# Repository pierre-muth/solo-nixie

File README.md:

# solo-nixie
A tiny single nixie tube clock, for LD995a or IN-16. USB powered, DS3231 RTC, built-in power-supply.

Details here https://pierremuth.wordpress.com/2021/12/11/a-cute-little-single-tube-nixie-clock/

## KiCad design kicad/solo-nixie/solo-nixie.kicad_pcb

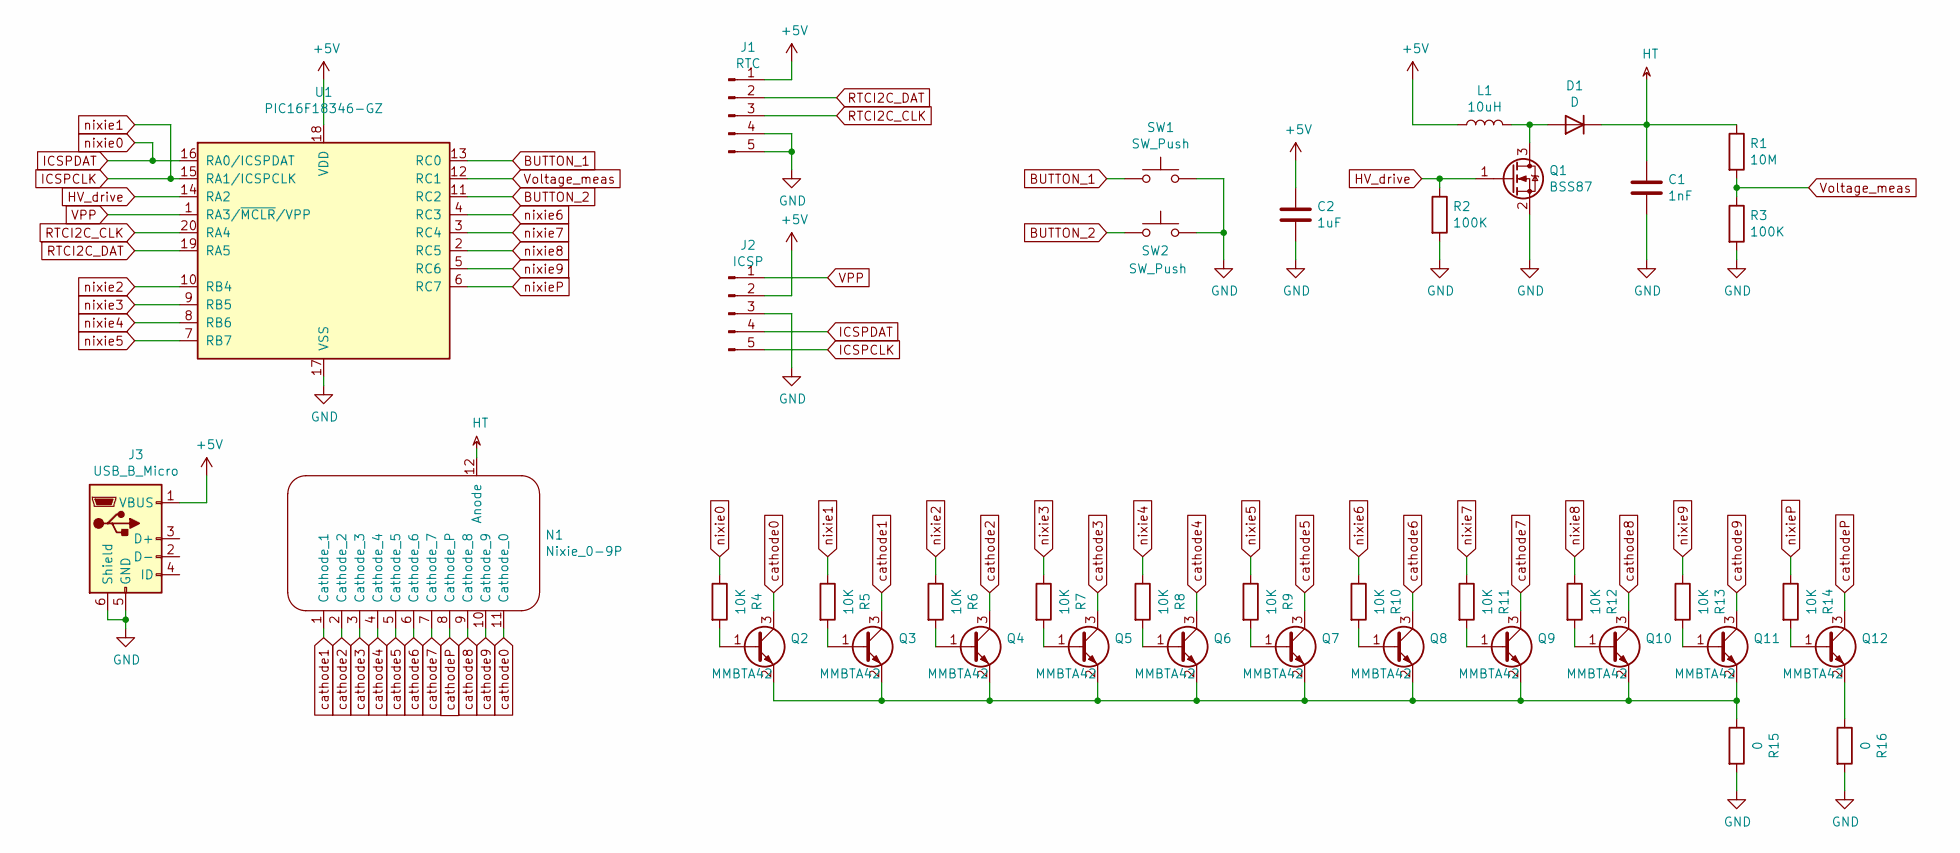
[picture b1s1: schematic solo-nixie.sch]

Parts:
C1: 1nF; 0805_HandSoldering
C2: 1uF; 0805_HandSoldering
D1: D; D_3220
J1: RTC; Pin_Header_RTC_5x2.54mm_SMD
J2: ICSP; PinHeader_1x05_P1.27mm_Vertical
J3: USB_B_Micro; USB_Micro-B_Wuerth-629105150521_CircularHoles
L1: 10uH; L_3216Metric
N1: Nixie_0-9P; LD8007
Q1: BSS87; CPH3
Q2, Q3, Q4, Q5, Q6, Q7, Q8, Q9, Q10, Q11, Q12: MMBTA42; SOT-23
R1: 10M; 0805_HandSoldering
R2, R3: 100K; 0805_HandSoldering
R4, R5, R6, R7, R8, R9, R10, R11, R12, R13, R14: 10K; 0805_HandSoldering
R15, R16: 0; 0805_HandSoldering
SW1, SW2: SW_Push; SW_SPST_EVQP7A
U1: PIC16F18346-GZ; UQFN-20-1EP_4x4mm_P0.5mm_EP2.8x2.8mm

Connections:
+5V: C2.1, J1.1, J2.2, J3.1 (VBUS), L1.1, U1.18 (VDD); also elsewhere on the board
BUTTON_1: SW1.1, U1.13 (RC0)
BUTTON_2: SW2.1, U1.11 (RC2)
GND: C1.2, C2.2, J1.4, J1.5, J2.3, J3.5 (GND), J3.6 (Shield), Q1.2 (S), R2.2, R3.2, R15.2, R16.2, SW1.2, SW2.2, U1.17 (VSS); also elsewhere on the board
HT: C1.1, D1.1 (K), N1.12 (Anode), R1.1
HV_drive: Q1.1 (G), R2.1, U1.14 (RA2)
ICSPCLK: J2.5, R5.1, U1.15 (RA1/ICSPCLK)
ICSPDAT: J2.4, R4.1, U1.16 (RA0/ICSPDAT)
unnamed: D1.2 (A), L1.2, Q1.3 (D)
unnamed: Q2.1 (B), R4.2
unnamed: Q3.1 (B), R5.2
unnamed: Q4.1 (B), R6.2
unnamed: Q5.1 (B), R7.2
unnamed: Q6.1 (B), R8.2
unnamed: Q7.1 (B), R9.2
unnamed: Q8.1 (B), R10.2
unnamed: Q9.1 (B), R11.2
unnamed: Q10.1 (B), R12.2
unnamed: Q2.2 (E), Q3.2 (E), Q4.2 (E), Q5.2 (E), Q6.2 (E), Q7.2 (E), Q8.2 (E), Q9.2 (E), Q10.2 (E), Q11.2 (E), R15.1
unnamed: Q11.1 (B), R13.2
unnamed: Q12.1 (B), R14.2
unnamed: Q12.2 (E), R16.1
RTCI2C_CLK: J1.3, U1.20 (RA4); also elsewhere on the board
RTCI2C_DAT: J1.2, U1.19 (RA5); also elsewhere on the board
VPP: J2.1, U1.1 (RA3/~MCLR~/VPP)
Voltage_meas: R1.2, R3.1, U1.12 (RC1)
cathode0: N1.11 (Cathode_0), Q2.3 (C)
cathode1: N1.1 (Cathode_1), Q3.3 (C)
cathode2: N1.2 (Cathode_2), Q4.3 (C)
cathode3: N1.3 (Cathode_3), Q5.3 (C)
cathode4: N1.4 (Cathode_4), Q6.3 (C)
cathode5: N1.5 (Cathode_5), Q7.3 (C)
cathode6: N1.6 (Cathode_6), Q8.3 (C)
cathode7: N1.7 (Cathode_7), Q9.3 (C)
cathode8: N1.9 (Cathode_8), Q10.3 (C)
cathode9: N1.10 (Cathode_9), Q11.3 (C)
cathodeP: N1.8 (Cathode_P), Q12.3 (C)
nixie2: R6.1, U1.10 (RB4)
nixie3: R7.1, U1.9 (RB5)
nixie4: R8.1, U1.8 (RB6)
nixie5: R9.1, U1.7 (RB7)
nixie6: R10.1, U1.4 (RC3)
nixie7: R11.1, U1.3 (RC4)
nixie8: R12.1, U1.2 (RC5)
nixie9: R13.1, U1.5 (RC6)
nixieP: R14.1, U1.6 (RC7)

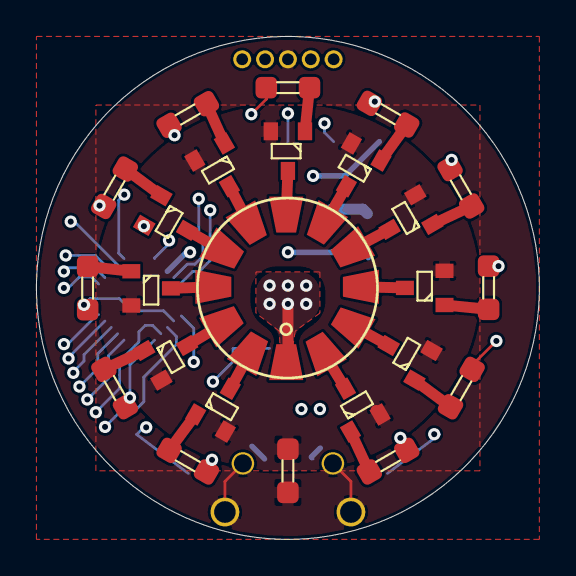
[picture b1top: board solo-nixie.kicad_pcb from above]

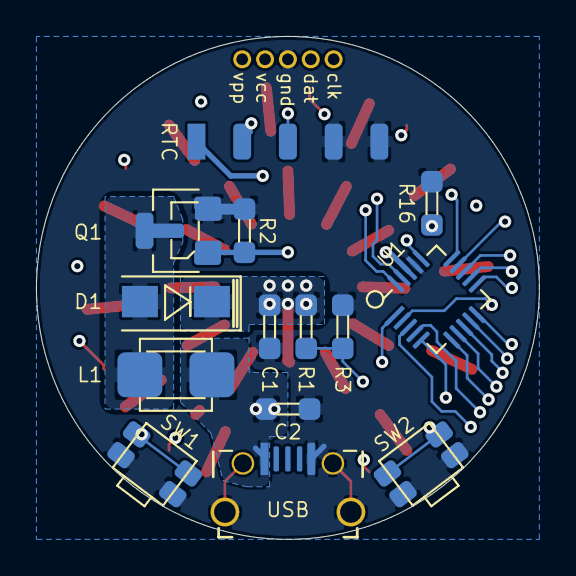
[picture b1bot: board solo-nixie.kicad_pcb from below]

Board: 4 copper layers, 27.9 x 27.9 mm, 39 parts (15 on the bottom side), 46 nets.

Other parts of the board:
RTC: RTC; Pin_Header_RTC_5x2.54mm_SMD
USB: USB_B_Micro; USB_Micro-B_Wuerth-629105150521_CircularHoles

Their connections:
+5V: RTC.1, USB.1; also elsewhere on the board
GND: RTC.4, RTC.5, USB.5, USB.6; also elsewhere on the board
RTCI2C_CLK: RTC.3; also elsewhere on the board
RTCI2C_DAT: RTC.2; also elsewhere on the board

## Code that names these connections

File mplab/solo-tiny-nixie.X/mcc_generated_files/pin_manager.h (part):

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// get/set nixie0 aliases
#define nixie0_TRIS                 TRISAbits.TRISA0
#define nixie0_LAT                  LATAbits.LATA0
#define nixie0_PORT                 PORTAbits.RA0
#define nixie0_WPU                  WPUAbits.WPUA0
#define nixie0_OD                   ODCONAbits.ODCA0
#define nixie0_ANS                  ANSELAbits.ANSA0
#define nixie0_SetHigh()            do { LATAbits.LATA0 = 1; } while(0)
#define nixie0_SetLow()             do { LATAbits.LATA0 = 0; } while(0)
#define nixie0_Toggle()             do { LATAbits.LATA0 = ~LATAbits.LATA0; } while(0)
#define nixie0_GetValue()           PORTAbits.RA0
#define nixie0_SetDigitalInput()    do { TRISAbits.TRISA0 = 1; } while(0)
#define nixie0_SetDigitalOutput()   do { TRISAbits.TRISA0 = 0; } while(0)
#define nixie0_SetPullup()          do { WPUAbits.WPUA0 = 1; } while(0)
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// get/set nixie1 aliases
#define nixie1_TRIS                 TRISAbits.TRISA1
#define nixie1_LAT                  LATAbits.LATA1
#define nixie1_PORT                 PORTAbits.RA1
#define nixie1_WPU                  WPUAbits.WPUA1
#define nixie1_OD                   ODCONAbits.ODCA1
#define nixie1_ANS                  ANSELAbits.ANSA1
#define nixie1_SetHigh()            do { LATAbits.LATA1 = 1; } while(0)
#define nixie1_SetLow()             do { LATAbits.LATA1 = 0; } while(0)
#define nixie1_Toggle()             do { LATAbits.LATA1 = ~LATAbits.LATA1; } while(0)
#define nixie1_GetValue()           PORTAbits.RA1
#define nixie1_SetDigitalInput()    do { TRISAbits.TRISA1 = 1; } while(0)
#define nixie1_SetDigitalOutput()   do { TRISAbits.TRISA1 = 0; } while(0)
#define nixie1_SetPullup()          do { WPUAbits.WPUA1 = 1; } while(0)
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#define RA2_SetHigh()            do { LATAbits.LATA2 = 1; } while(0)
#define RA2_SetLow()             do { LATAbits.LATA2 = 0; } while(0)
#define RA2_Toggle()             do { LATAbits.LATA2 = ~LATAbits.LATA2; } while(0)
#define RA2_GetValue()              PORTAbits.RA2
#define RA2_SetDigitalInput()    do { TRISAbits.TRISA2 = 1; } while(0)
#define RA2_SetDigitalOutput()   do { TRISAbits.TRISA2 = 0; } while(0)
#define RA2_SetPullup()             do { WPUAbits.WPUA2 = 1; } while(0)
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#define RA4_SetHigh()            do { LATAbits.LATA4 = 1; } while(0)
#define RA4_SetLow()             do { LATAbits.LATA4 = 0; } while(0)
#define RA4_Toggle()             do { LATAbits.LATA4 = ~LATAbits.LATA4; } while(0)
#define RA4_GetValue()              PORTAbits.RA4
#define RA4_SetDigitalInput()    do { TRISAbits.TRISA4 = 1; } while(0)
#define RA4_SetDigitalOutput()   do { TRISAbits.TRISA4 = 0; } while(0)
#define RA4_SetPullup()             do { WPUAbits.WPUA4 = 1; } while(0)
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#define RA5_SetHigh()            do { LATAbits.LATA5 = 1; } while(0)
#define RA5_SetLow()             do { LATAbits.LATA5 = 0; } while(0)
#define RA5_Toggle()             do { LATAbits.LATA5 = ~LATAbits.LATA5; } while(0)
#define RA5_GetValue()              PORTAbits.RA5
#define RA5_SetDigitalInput()    do { TRISAbits.TRISA5 = 1; } while(0)
#define RA5_SetDigitalOutput()   do { TRISAbits.TRISA5 = 0; } while(0)
#define RA5_SetPullup()             do { WPUAbits.WPUA5 = 1; } while(0)
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// get/set nixie2 aliases
#define nixie2_TRIS                 TRISBbits.TRISB4
#define nixie2_LAT                  LATBbits.LATB4
#define nixie2_PORT                 PORTBbits.RB4
#define nixie2_WPU                  WPUBbits.WPUB4
#define nixie2_OD                   ODCONBbits.ODCB4
#define nixie2_ANS                  ANSELBbits.ANSB4
#define nixie2_SetHigh()            do { LATBbits.LATB4 = 1; } while(0)
#define nixie2_SetLow()             do { LATBbits.LATB4 = 0; } while(0)
#define nixie2_Toggle()             do { LATBbits.LATB4 = ~LATBbits.LATB4; } while(0)
#define nixie2_GetValue()           PORTBbits.RB4
#define nixie2_SetDigitalInput()    do { TRISBbits.TRISB4 = 1; } while(0)
#define nixie2_SetDigitalOutput()   do { TRISBbits.TRISB4 = 0; } while(0)
#define nixie2_SetPullup()          do { WPUBbits.WPUB4 = 1; } while(0)
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// get/set nixie3 aliases
#define nixie3_TRIS                 TRISBbits.TRISB5
#define nixie3_LAT                  LATBbits.LATB5
#define nixie3_PORT                 PORTBbits.RB5
#define nixie3_WPU                  WPUBbits.WPUB5
#define nixie3_OD                   ODCONBbits.ODCB5
#define nixie3_ANS                  ANSELBbits.ANSB5
#define nixie3_SetHigh()            do { LATBbits.LATB5 = 1; } while(0)
#define nixie3_SetLow()             do { LATBbits.LATB5 = 0; } while(0)
#define nixie3_Toggle()             do { LATBbits.LATB5 = ~LATBbits.LATB5; } while(0)
#define nixie3_GetValue()           PORTBbits.RB5
#define nixie3_SetDigitalInput()    do { TRISBbits.TRISB5 = 1; } while(0)
#define nixie3_SetDigitalOutput()   do { TRISBbits.TRISB5 = 0; } while(0)
#define nixie3_SetPullup()          do { WPUBbits.WPUB5 = 1; } while(0)
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// get/set nixie4 aliases
#define nixie4_TRIS                 TRISBbits.TRISB6
#define nixie4_LAT                  LATBbits.LATB6
#define nixie4_PORT                 PORTBbits.RB6
#define nixie4_WPU                  WPUBbits.WPUB6
#define nixie4_OD                   ODCONBbits.ODCB6
#define nixie4_ANS                  ANSELBbits.ANSB6
#define nixie4_SetHigh()            do { LATBbits.LATB6 = 1; } while(0)
#define nixie4_SetLow()             do { LATBbits.LATB6 = 0; } while(0)
#define nixie4_Toggle()             do { LATBbits.LATB6 = ~LATBbits.LATB6; } while(0)
#define nixie4_GetValue()           PORTBbits.RB6
#define nixie4_SetDigitalInput()    do { TRISBbits.TRISB6 = 1; } while(0)
#define nixie4_SetDigitalOutput()   do { TRISBbits.TRISB6 = 0; } while(0)
#define nixie4_SetPullup()          do { WPUBbits.WPUB6 = 1; } while(0)
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// get/set nixie5 aliases
#define nixie5_TRIS                 TRISBbits.TRISB7
#define nixie5_LAT                  LATBbits.LATB7
#define nixie5_PORT                 PORTBbits.RB7
#define nixie5_WPU                  WPUBbits.WPUB7
#define nixie5_OD                   ODCONBbits.ODCB7
#define nixie5_ANS                  ANSELBbits.ANSB7
#define nixie5_SetHigh()            do { LATBbits.LATB7 = 1; } while(0)
#define nixie5_SetLow()             do { LATBbits.LATB7 = 0; } while(0)
#define nixie5_Toggle()             do { LATBbits.LATB7 = ~LATBbits.LATB7; } while(0)
#define nixie5_GetValue()           PORTBbits.RB7
#define nixie5_SetDigitalInput()    do { TRISBbits.TRISB7 = 1; } while(0)
#define nixie5_SetDigitalOutput()   do { TRISBbits.TRISB7 = 0; } while(0)
#define nixie5_SetPullup()          do { WPUBbits.WPUB7 = 1; } while(0)
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// get/set Button1 aliases
#define Button1_TRIS                 TRISCbits.TRISC0
#define Button1_LAT                  LATCbits.LATC0
#define Button1_PORT                 PORTCbits.RC0
#define Button1_WPU                  WPUCbits.WPUC0
#define Button1_OD                   ODCONCbits.ODCC0
#define Button1_ANS                  ANSELCbits.ANSC0
#define Button1_SetHigh()            do { LATCbits.LATC0 = 1; } while(0)
#define Button1_SetLow()             do { LATCbits.LATC0 = 0; } while(0)
#define Button1_Toggle()             do { LATCbits.LATC0 = ~LATCbits.LATC0; } while(0)
#define Button1_GetValue()           PORTCbits.RC0
#define Button1_SetDigitalInput()    do { TRISCbits.TRISC0 = 1; } while(0)
#define Button1_SetDigitalOutput()   do { TRISCbits.TRISC0 = 0; } while(0)
#define Button1_SetPullup()          do { WPUCbits.WPUC0 = 1; } while(0)
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#define RC1_SetHigh()            do { LATCbits.LATC1 = 1; } while(0)
#define RC1_SetLow()             do { LATCbits.LATC1 = 0; } while(0)
#define RC1_Toggle()             do { LATCbits.LATC1 = ~LATCbits.LATC1; } while(0)
#define RC1_GetValue()              PORTCbits.RC1
#define RC1_SetDigitalInput()    do { TRISCbits.TRISC1 = 1; } while(0)
#define RC1_SetDigitalOutput()   do { TRISCbits.TRISC1 = 0; } while(0)
#define RC1_SetPullup()             do { WPUCbits.WPUC1 = 1; } while(0)
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// get/set Button2 aliases
#define Button2_TRIS                 TRISCbits.TRISC2
#define Button2_LAT                  LATCbits.LATC2
#define Button2_PORT                 PORTCbits.RC2
#define Button2_WPU                  WPUCbits.WPUC2
#define Button2_OD                   ODCONCbits.ODCC2
#define Button2_ANS                  ANSELCbits.ANSC2
#define Button2_SetHigh()            do { LATCbits.LATC2 = 1; } while(0)
#define Button2_SetLow()             do { LATCbits.LATC2 = 0; } while(0)
#define Button2_Toggle()             do { LATCbits.LATC2 = ~LATCbits.LATC2; } while(0)
#define Button2_GetValue()           PORTCbits.RC2
#define Button2_SetDigitalInput()    do { TRISCbits.TRISC2 = 1; } while(0)
#define Button2_SetDigitalOutput()   do { TRISCbits.TRISC2 = 0; } while(0)
#define Button2_SetPullup()          do { WPUCbits.WPUC2 = 1; } while(0)
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// get/set nixie6 aliases
#define nixie6_TRIS                 TRISCbits.TRISC3
#define nixie6_LAT                  LATCbits.LATC3
#define nixie6_PORT                 PORTCbits.RC3
#define nixie6_WPU                  WPUCbits.WPUC3
#define nixie6_OD                   ODCONCbits.ODCC3
#define nixie6_ANS                  ANSELCbits.ANSC3
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

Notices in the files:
mplab/solo-tiny-nixie.X/mcc_generated_files/pin_manager.h:
(c) 2018 Microchip Technology Inc. and its subsidiaries.
